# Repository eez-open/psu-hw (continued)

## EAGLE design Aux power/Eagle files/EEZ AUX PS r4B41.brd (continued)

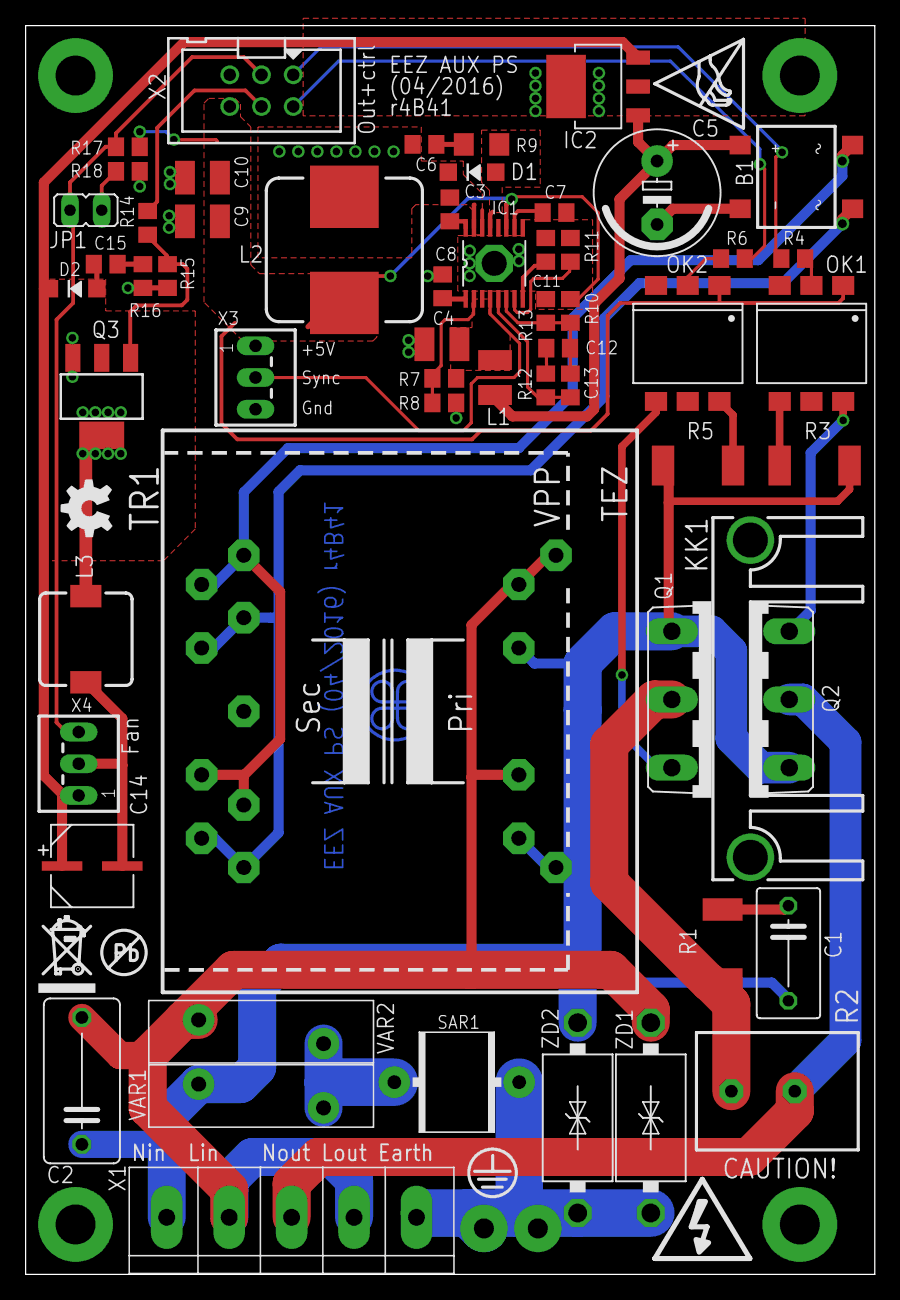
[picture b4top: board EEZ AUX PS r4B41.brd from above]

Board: 3 copper layers, 68.0 x 100.0 mm, 62 parts (0 on the bottom side), 42 nets.

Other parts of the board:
EEZ_SIGNATURE: SIGNATURESMALL; SIGNATURE_5MM
U$2: RECYCLE_BIN1/8
U$3: PB_SMALL
U$4: ESD_SYMBOL
